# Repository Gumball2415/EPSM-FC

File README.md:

# EPSM-FC

Expansion Port Sound Module for the Famicom

## About

Work in progress!!

This is a version of the EPSM ported for use with the Famicom.

The challenge with the Famicom version is that the device no longer has access
to the extra control signals on the NES expansion port. Most relevant, OUT1,
CPU_A15, and all the EXP pins. This project aims to solve this using extra logic
that can recreate the necessary signals for addressing the EPSM.

## License

This design is licensed under the TAPR Open Hardware License.\
For resale, please contact Pierre Althinsson (Perkka).

Original EPSM is Copyright (C) 2021-2025 Pierre Althinson.\
EPSM-FC is Copyright (C) 2022-2025 Persune.

## Usage

- [NESDev wiki](https://www.nesdev.org/wiki/Expansion_Port_Sound_Module)
- Also see [the original EPSM repo](https://github.com/Perkka2/EPSM/)

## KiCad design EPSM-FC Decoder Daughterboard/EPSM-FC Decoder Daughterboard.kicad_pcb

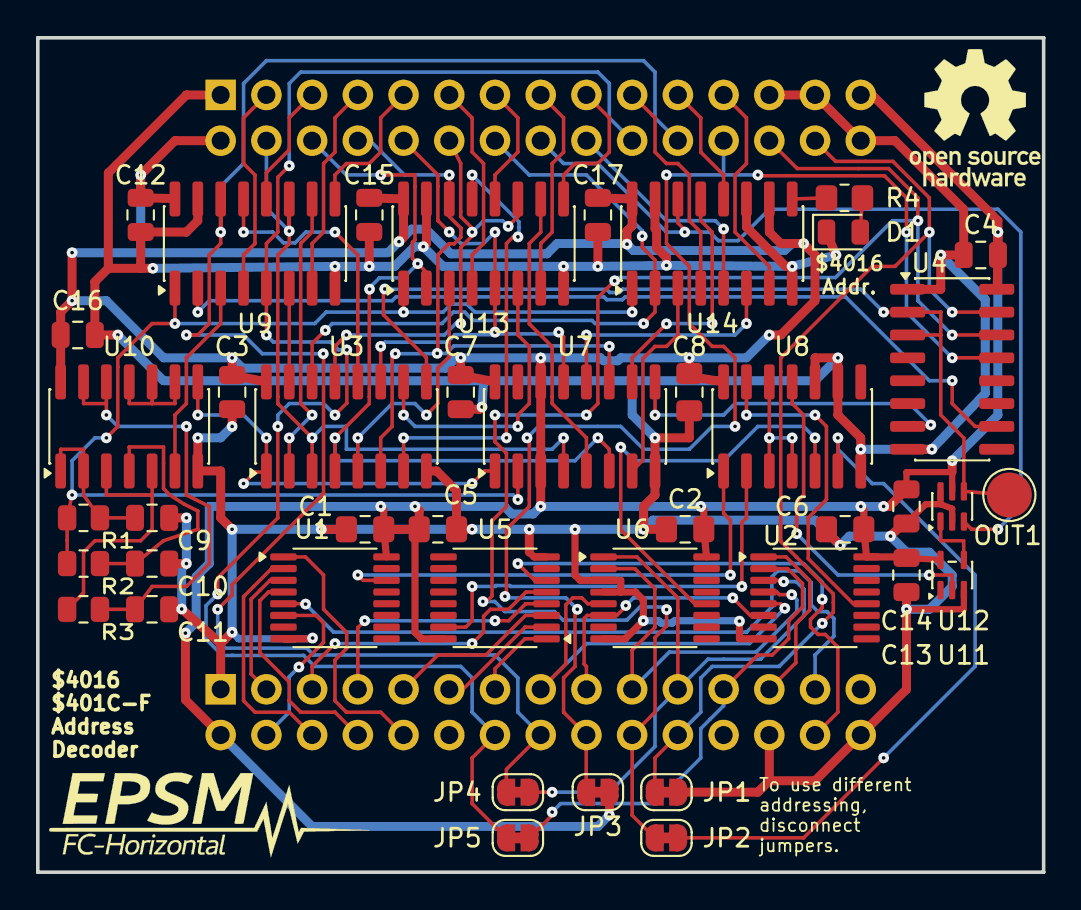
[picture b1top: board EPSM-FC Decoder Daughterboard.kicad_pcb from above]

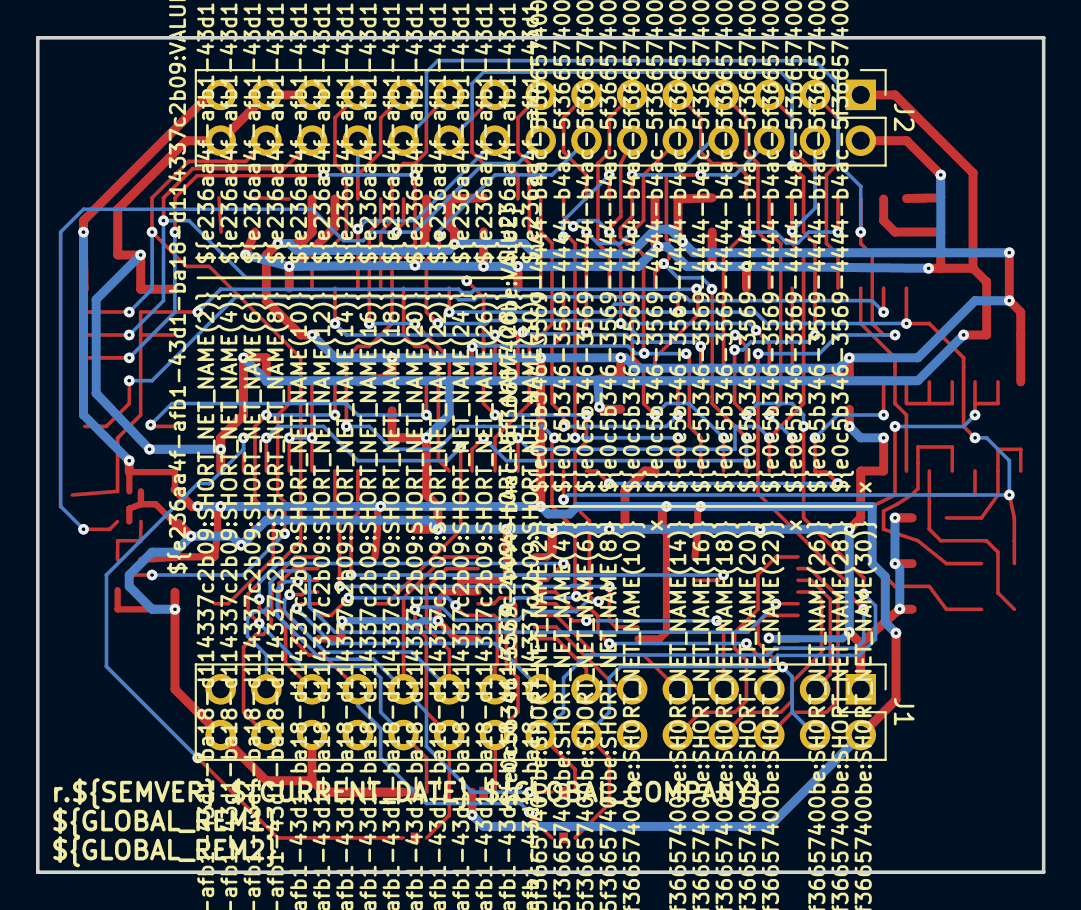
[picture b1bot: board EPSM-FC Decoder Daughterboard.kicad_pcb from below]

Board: 2 copper layers, 55.9 x 46.4 mm, 46 parts (2 on the bottom side), 75 nets.

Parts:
C1, C2, C5, C6, C8: 0.1uF; C_0805_2012Metric_Pad1.18x1.45mm_HandSolder
C3, C4, C7, C12, C13, C14, C15, C16, C17: 0.1u; C_0805_2012Metric
C9, C10, C11: 68p; C_0805_2012Metric
D1: PINK; LED_0805_2012Metric
J1: EPSM_ADDR; PinHeader_2x15_P2.54mm_Vertical
J2: EPSM_DATA; PinHeader_2x15_P2.54mm_Vertical
JP1, JP2, JP3, JP4, JP5: SolderJumper-2_P1.3mm_Bridged_RoundedPad1.0x1.5mm
R1: 3K; R_0805_2012Metric
R2, R3: 1K; R_0805_2012Metric
R4: 330; R_0805_2012Metric_Pad1.20x1.40mm_HandSolder
Ref**: Val**; oshw-logo
Ref**#2: Val**; EPSM_silkscreen
TP1: OUT1; TestPoint_Pad_D2.5mm
U1, U2, U5, U6: 74HC138; TSSOP-16_4.4x5mm_P0.65mm
U3, U7: 74HC174; SOIC-16_3.9x9.9mm_P1.27mm
U4: 74HC139; SOIC-16_3.9x9.9mm_P1.27mm
U8: 74HC32; SOIC-14_3.9x8.7mm_P1.27mm
U9, U13, U14: 74HC157; SOIC-16_3.9x9.9mm_P1.27mm
U10: 74HC132; SOIC-14_3.9x8.7mm_P1.27mm
U11: 74LVC1GU04; SOT-353_SC-70-5
U12: 74LVC1G373; SOT-363_SC-70-6

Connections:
/$40xx_W_~CE: U8.3, U8.4, U8.12
/$40xx_~W_A: U1.14 (~Y1), U8.1
/$40xx_~W_B: U5.15 (~Y0), U8.2
/$401C-F_~CE: U6.12 (~Y3), U8.5
/$401CFW~CE: JP2.1 (A), U8.6
/$4016_P: R1.1, R2.1, U7.2 (Q0), U9.1 (S), U13.1 (S), U14.1 (S)
/$4016_W_CE: U11.4, U12.1 (LE)
/$4016_W_~CE: U8.11, U11.2
/$4016_~CE: U2.12 (~Y3), U8.13
/$4016_~P_DL: R3.1, U10.3, U10.5
/B_CPU_A0: J1.25, U2.1 (A0)
/B_CPU_A1: J1.23, JP5.1 (A), U2.2 (A1)
/B_CPU_A2: J1.21, JP4.1 (A), U2.3 (A2), U6.1 (A0)
/B_CPU_A3: J1.19, U2.4 (~E0), U6.2 (A1)
/B_CPU_A4: J1.17, U2.6 (E2), U6.6 (E2)
/B_CPU_A5: J1.15, U2.5 (~E1), U6.5 (~E1)
/B_CPU_A6: J1.13, U5.1 (A0)
/B_CPU_A7: J1.11, U5.2 (A1)
/B_CPU_A8: J1.9, U5.3 (A2)
/B_CPU_A9: J1.7, U5.4 (~E0)
/B_CPU_A10: J1.5, U5.5 (~E1)
/B_CPU_A11: J1.3, U1.3 (A2)
/B_CPU_A12: J1.6, U1.2 (A1)
/B_CPU_A13: J1.8, U1.4 (~E0)
/B_CPU_A14: J1.10, U1.1 (A0)
/B_CPU_D0: J2.18, U14.5 (I0b)
/B_CPU_D1: J2.16, U12.3 (D), U14.14 (I0d)
/B_CPU_D2: J2.14, U3.14 (D5), U14.2 (I0a)
/B_CPU_D3: J2.12, U3.13 (D4), U13.11 (I0c)
/B_CPU_D4: J2.10, U3.11 (D3), U7.13 (D4), U13.5 (I0b)
/B_CPU_D5: J2.8, U3.6 (D2), U7.11 (D3), U13.14 (I0d)
/B_CPU_D6: J2.6, U3.4 (D1), U7.6 (D2), U13.2 (I0a)
/B_CPU_D7: J2.4, U3.3 (D0), U7.4 (D1), U9.11 (I0c)
/B_CPU_R~W: J1.27, U1.5 (~E1)
/B_M2: J1.4, U1.6 (E2)
/B_~ROMSEL: J1.28, U5.6 (E2)
/EPSM_A0: J1.16, J2.22, JP4.2 (B), U9.14 (I0d)
/EPSM_A1: J1.14, J2.20, JP5.2 (B), U9.5 (I0b)
/EPSM_CE3: J1.18, J2.24, JP3.2 (B), U4.13 (A1)
/EPSM_~CE1: J1.22, J2.28, JP1.2 (B), U4.15 (E)
/EPSM_~CE2: J1.20, J2.26, JP2.2 (B), U4.14 (A0)
/EPSM_~CS: U4.10 (O2), U9.2 (I0a)
/OUT1: TP1.1 (1_1), U3.9 (Cp), U4.2 (A0), U4.3 (A1), U12.4 (Q)
/S_A0: U3.12 (Q4), U9.13 (I1d)
/S_A1: U3.15 (Q5), U9.6 (I1b)
/S_CPU_D0: U7.12 (Q4), U14.6 (I1b)
/S_CPU_D1: U7.10 (Q3), U14.13 (I1d)
/S_CPU_D2: U7.7 (Q2), U14.3 (I1a)
/S_CPU_D3: U7.5 (Q1), U13.10 (I1c)
/S_CPU_D4: U3.10 (Q3), U13.6 (I1b)
/S_CPU_D5: U3.7 (Q2), U13.13 (I1d)
/S_CPU_D6: U3.5 (Q1), U13.3 (I1a)
/S_CPU_D7: U3.2 (Q0), U9.10 (I1c)
/S_~CS: U9.3 (I1a), U10.6
/S_~RST: U3.1 (~Mr), U7.1 (~Mr), U10.8
/YM_A0: J2.5, U9.12 (Zd)
/YM_A1: J2.7, U9.7 (Zb)
/YM_D0: J2.23, U14.7 (Zb)
/YM_D1: J2.21, U14.12 (Zd)
/YM_D2: J2.19, U14.4 (Za)
/YM_D3: J2.17, U13.9 (Zc)
/YM_D4: J2.15, U13.7 (Zb)
/YM_D5: J2.13, U13.12 (Zd)
/YM_D6: J2.11, U13.4 (Za)
/YM_D7: J2.9, U9.9 (Zc)
/YM_~CS: J2.3, U9.4 (Za)
/~OUT1: U4.7 (O3), U7.9 (Cp)
GND: C1.1, C2.1, C3.1, C4.1, C5.1, C6.1, C7.1, C8.1, C9.2, C10.2, C11.2, C12.1, C13.1, C14.1, C15.1, C16.1, C17.1, D1.1 (K), J1.1, J1.26, J1.30, J2.1, J2.25, J2.27, J2.30, JP1.1 (A), U1.8 (GND), U2.8 (GND), U3.8 (GND), U4.1 (E), U4.8 (GND), U5.8 (GND), U6.3 (A2), U6.4 (~E0), U6.8 (GND), U7.8 (GND), U8.7 (GND), U8.9, U8.10, U9.8 (GND), U9.15 (E), U10.7 (GND), U11.3 (GND), U12.2 (GND), U12.6 (~OE), U13.8 (GND), U13.15 (E), U14.8 (GND), U14.11 (I0c), U14.15 (E)
unnamed: C9.1, R1.2, U10.1, U10.2
unnamed: C10.1, R2.2, U10.4
unnamed: C11.1, R3.2, U10.12, U10.13
unnamed: D1.2 (A), R4.2
unnamed: U10.9, U10.10, U10.11
unnamed: R4.1, U14.9 (Zc)
VCC: C1.2, C2.2, C3.2, C4.2, C5.2, C6.2, C7.2, C8.2, C12.2, C13.2, C14.2, C15.2, C16.2, C17.2, J1.2, J2.2, J2.29, JP3.1 (A), U1.16 (VCC), U2.16 (VCC), U3.16 (VCC), U4.16 (VCC), U5.16 (VCC), U6.16 (VCC), U7.3 (D0), U7.14 (D5), U7.16 (VCC), U8.14 (VCC), U9.16 (VCC), U10.14 (VCC), U11.5 (VCC), U12.5 (VCC), U13.16 (VCC), U14.10 (I1c), U14.16 (VCC)

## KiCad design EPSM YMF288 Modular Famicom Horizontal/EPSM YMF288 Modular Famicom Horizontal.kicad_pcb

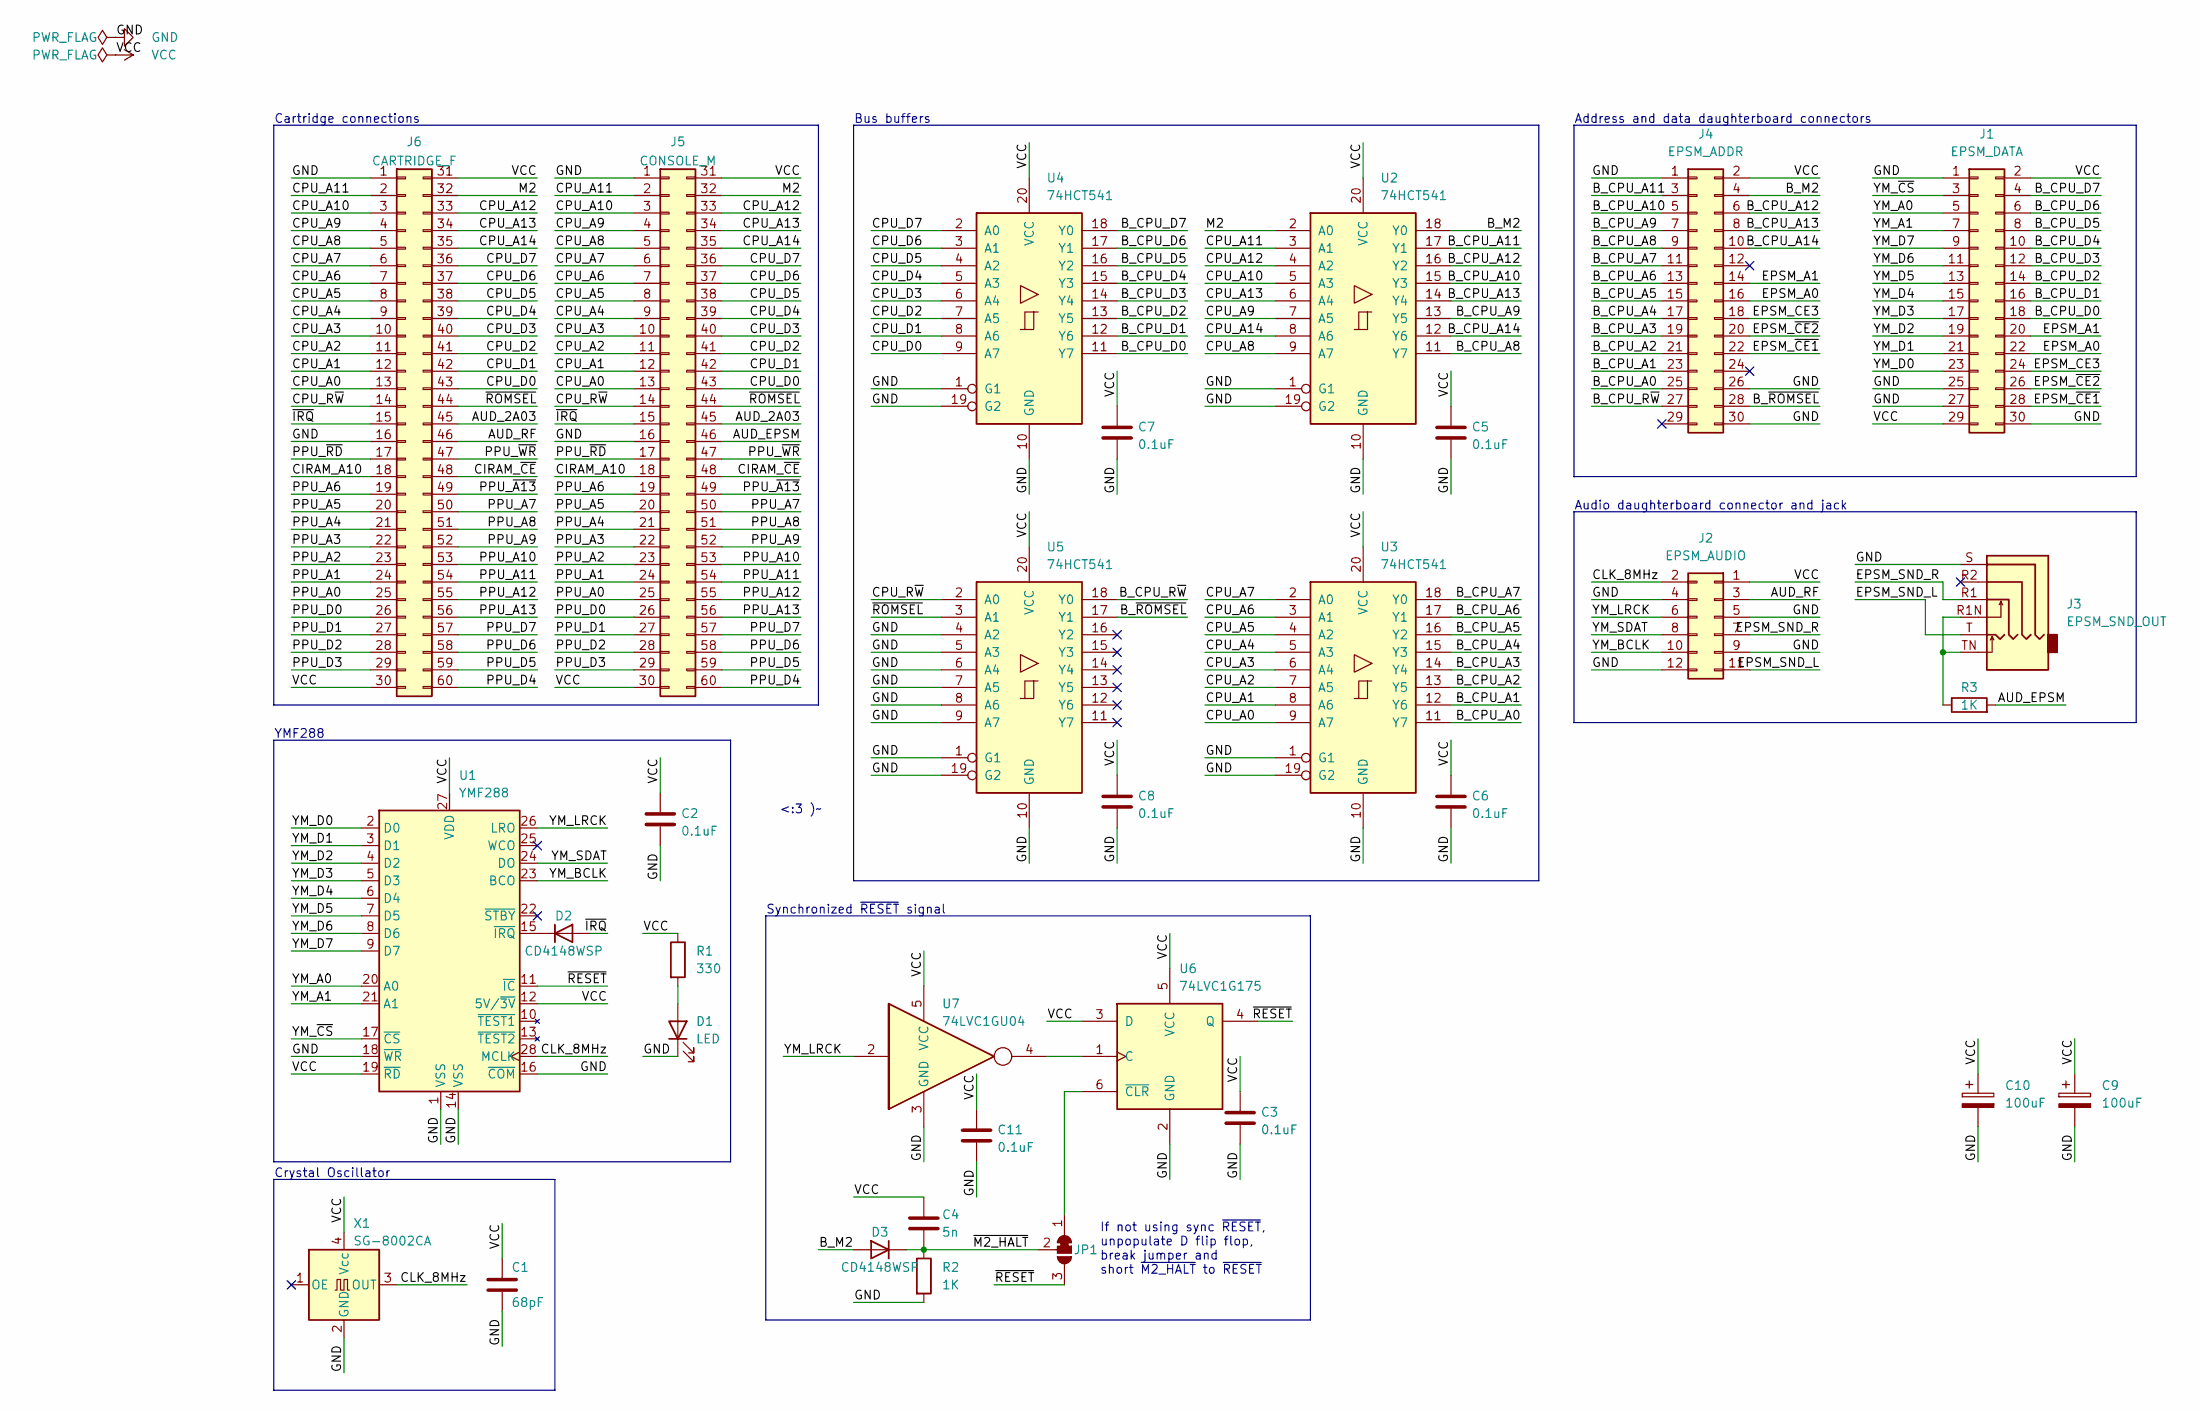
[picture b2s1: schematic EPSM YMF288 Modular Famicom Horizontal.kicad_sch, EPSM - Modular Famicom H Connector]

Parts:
C1: 68pF; C_0805_2012Metric_Pad1.18x1.45mm_HandSolder
C2, C3, C5, C6, C7, C8, C11: 0.1uF; C_0805_2012Metric_Pad1.18x1.45mm_HandSolder
C4: 5n; C_0805_2012Metric_Pad1.18x1.45mm_HandSolder
C9, C10: 100uF; CP_Elec_6.3x5.4
D1: LED; LED_0805_2012Metric
D2, D3: CD4148WSP; D_0805_2012Metric
J1: EPSM_DATA; PinSocket_2x15_P2.54mm_Vertical_SMD
J2: EPSM_AUDIO; PinSocket_2x06_P2.54mm_Vertical_SMD
J3: EPSM_SND_OUT; Jack_3.5mm_PJ311_Horizontal
J4: EPSM_ADDR; PinSocket_2x15_P2.54mm_Vertical_SMD
J5: CONSOLE_M; HVC-ETROM-01
J6: CARTRIDGE_F; FC_CONN_F
JP1: SolderJumper-3_P1.3mm_Bridged12_Pad1.0x1.5mm
R1: 330; R_0805_2012Metric_Pad1.20x1.40mm_HandSolder
R2, R3: 1K; R_0805_2012Metric_Pad1.20x1.40mm_HandSolder
U1: YMF288; SOP-28_8.4x18.1mm_P1.27mm
U2, U3, U4, U5: 74HCT541; TSSOP-20_4.4x6.5mm_P0.65mm
U6: 74LVC1G175; SOT-363_SC-70-6; LCSC C52145624
U7: 74LVC1GU04; SOT-353_SC-70-5; LCSC C53114303
X1: SG-8002CA; Oscillator_SMD_Abracon_ASV-4Pin_7.0x5.1mm

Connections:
/AUD_2A03: J5.45, J6.45
/AUD_EPSM: J5.46, R3.2
/AUD_RF: J2.3, J6.46
/B_CPU_A0: J4.25, U3.11 (Y7)
/B_CPU_A1: J4.23, U3.12 (Y6)
/B_CPU_A2: J4.21, U3.13 (Y5)
/B_CPU_A3: J4.19, U3.14 (Y4)
/B_CPU_A4: J4.17, U3.15 (Y3)
/B_CPU_A5: J4.15, U3.16 (Y2)
/B_CPU_A6: J4.13, U3.17 (Y1)
/B_CPU_A7: J4.11, U3.18 (Y0)
/B_CPU_A8: J4.9, U2.11 (Y7)
/B_CPU_A9: J4.7, U2.13 (Y5)
/B_CPU_A10: J4.5, U2.15 (Y3)
/B_CPU_A11: J4.3, U2.17 (Y1)
/B_CPU_A12: J4.6, U2.16 (Y2)
/B_CPU_A13: J4.8, U2.14 (Y4)
/B_CPU_A14: J4.10, U2.12 (Y6)
/B_CPU_D0: J1.18, U4.11 (Y7)
/B_CPU_D1: J1.16, U4.12 (Y6)
/B_CPU_D2: J1.14, U4.13 (Y5)
/B_CPU_D3: J1.12, U4.14 (Y4)
/B_CPU_D4: J1.10, U4.15 (Y3)
/B_CPU_D5: J1.8, U4.16 (Y2)
/B_CPU_D6: J1.6, U4.17 (Y1)
/B_CPU_D7: J1.4, U4.18 (Y0)
/B_CPU_R~W: J4.27, U5.18 (Y0)
/B_M2: D3.2 (A), J4.4, U2.18 (Y0)
/B_~ROMSEL: J4.28, U5.17 (Y1)
/CIRAM_A10: J5.18, J6.18
/CIRAM_~CE: J5.48, J6.48
/CLK_8MHz: J2.2, U1.28 (MCLK), X1.3 (OUT)
/CPU_A0: J5.13, J6.13, U3.9 (A7)
/CPU_A1: J5.12, J6.12, U3.8 (A6)
/CPU_A2: J5.11, J6.11, U3.7 (A5)
/CPU_A3: J5.10, J6.10, U3.6 (A4)
/CPU_A4: J5.9, J6.9, U3.5 (A3)
/CPU_A5: J5.8, J6.8, U3.4 (A2)
/CPU_A6: J5.7, J6.7, U3.3 (A1)
/CPU_A7: J5.6, J6.6, U3.2 (A0)
/CPU_A8: J5.5, J6.5, U2.9 (A7)
/CPU_A9: J5.4, J6.4, U2.7 (A5)
/CPU_A10: J5.3, J6.3, U2.5 (A3)
/CPU_A11: J5.2, J6.2, U2.3 (A1)
/CPU_A12: J5.33, J6.33, U2.4 (A2)
/CPU_A13: J5.34, J6.34, U2.6 (A4)
/CPU_A14: J5.35, J6.35, U2.8 (A6)
/CPU_D0: J5.43, J6.43, U4.9 (A7)
/CPU_D1: J5.42, J6.42, U4.8 (A6)
/CPU_D2: J5.41, J6.41, U4.7 (A5)
/CPU_D3: J5.40, J6.40, U4.6 (A4)
/CPU_D4: J5.39, J6.39, U4.5 (A3)
/CPU_D5: J5.38, J6.38, U4.4 (A2)
/CPU_D6: J5.37, J6.37, U4.3 (A1)
/CPU_D7: J5.36, J6.36, U4.2 (A0)
/CPU_R~W: J5.14, J6.14, U5.2 (A0)
/EPSM_A0: J1.22, J4.16
/EPSM_A1: J1.20, J4.14
/EPSM_CE3: J1.24, J4.18
/EPSM_SND_L: J2.11, J3.T
/EPSM_SND_R: J2.7, J3.R1
/EPSM_~CE1: J1.28, J4.22
/EPSM_~CE2: J1.26, J4.20
/M2: J5.32, J6.32, U2.2 (A0)
/PPU_A0: J5.25, J6.25
/PPU_A1: J5.24, J6.24
/PPU_A2: J5.23, J6.23
/PPU_A3: J5.22, J6.22
/PPU_A4: J5.21, J6.21
/PPU_A5: J5.20, J6.20
/PPU_A6: J5.19, J6.19
/PPU_A7: J5.50, J6.50
/PPU_A8: J5.51, J6.51
/PPU_A9: J5.52, J6.52
/PPU_A10: J5.53, J6.53
/PPU_A11: J5.54, J6.54
/PPU_A12: J5.55, J6.55
/PPU_A13: J5.56, J6.56
/PPU_D0: J5.26, J6.26
/PPU_D1: J5.27, J6.27
/PPU_D2: J5.28, J6.28
/PPU_D3: J5.29, J6.29
/PPU_D4: J5.60, J6.60
/PPU_D5: J5.59, J6.59
/PPU_D6: J5.58, J6.58
/PPU_D7: J5.57, J6.57
/PPU_~A13: J5.49, J6.49
/PPU_~RD: J5.17, J6.17
/PPU_~WR: J5.47, J6.47
/YM_A0: J1.5, U1.20 (A0)
/YM_A1: J1.7, U1.21 (A1)
/YM_BCLK: J2.10, U1.23 (BCO)
/YM_D0: J1.23, U1.2 (D0)
/YM_D1: J1.21, U1.3 (D1)
/YM_D2: J1.19, U1.4 (D2)
/YM_D3: J1.17, U1.5 (D3)
/YM_D4: J1.15, U1.6 (D4)
/YM_D5: J1.13, U1.7 (D5)
/YM_D6: J1.11, U1.8 (D6)
/YM_D7: J1.9, U1.9 (D7)
/YM_LRCK: J2.6, U1.26 (LRO), U7.2
/YM_SDAT: J2.8, U1.24 (DO)
/YM_~CS: J1.3, U1.17 (~CS)
/~IRQ: D2.2 (A), J5.15, J6.15
/~M2_HALT: C4.1, D3.1 (K), JP1.2 (C), R2.1
/~RESET: JP1.3 (B), U1.11 (~IC), U6.4 (Q)
/~ROMSEL: J5.44, J6.44, U5.3 (A1)
GND: C1.2, C2.1, C3.1, C5.1, C6.1, C7.1, C8.1, C9.2, C10.2, C11.1, D1.1 (K), J1.1, J1.25, J1.27, J1.30, J2.4, J2.5, J2.9, J2.12, J3.S, J4.1, J4.26, J4.30, J5.1, J5.16, J6.1, J6.16, R2.2, U1.1 (VSS), U1.14 (VSS), U1.16 (~COM), U1.18 (~WR), U2.1 (G1), U2.10 (GND), U2.19 (G2), U3.1 (G1), U3.10 (GND), U3.19 (G2), U4.1 (G1), U4.10 (GND), U4.19 (G2), U5.1 (G1), U5.4 (A2), U5.5 (A3), U5.6 (A4), U5.7 (A5), U5.8 (A6), U5.9 (A7), U5.10 (GND), U5.19 (G2), U6.2 (GND), U7.3 (GND), X1.2 (GND)
unnamed: D1.2 (A), R1.2
unnamed: D2.1 (K), U1.15 (~IRQ)
unnamed: J3.R1N, J3.TN, R3.1
unnamed: JP1.1 (A), U6.6 (~CLR)
unnamed: U6.1 (C), U7.4
VCC: C1.1, C2.2, C3.2, C4.2, C5.2, C6.2, C7.2, C8.2, C9.1, C10.1, C11.2, J1.2, J1.29, J2.1, J4.2, J5.30, J5.31, J6.30, J6.31, R1.1, U1.12 (5V/~3V), U1.19 (~RD), U1.27 (VDD), U2.20 (VCC), U3.20 (VCC), U4.20 (VCC), U5.20 (VCC), U6.3 (D), U6.5 (VCC), U7.5 (VCC), X1.4 (Vcc)

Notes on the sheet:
Bus buffers
Synchronized ~{RESET} signal
If not using sync ~{RESET}, unpopulate D flip flop, break jumper and short ~{M2_HALT} to ~{RESET}
Address and data daughterboard connectors
<:3 )~
YMF288
Crystal Oscillator
Audio daughterboard connector and jack
Cartridge connections

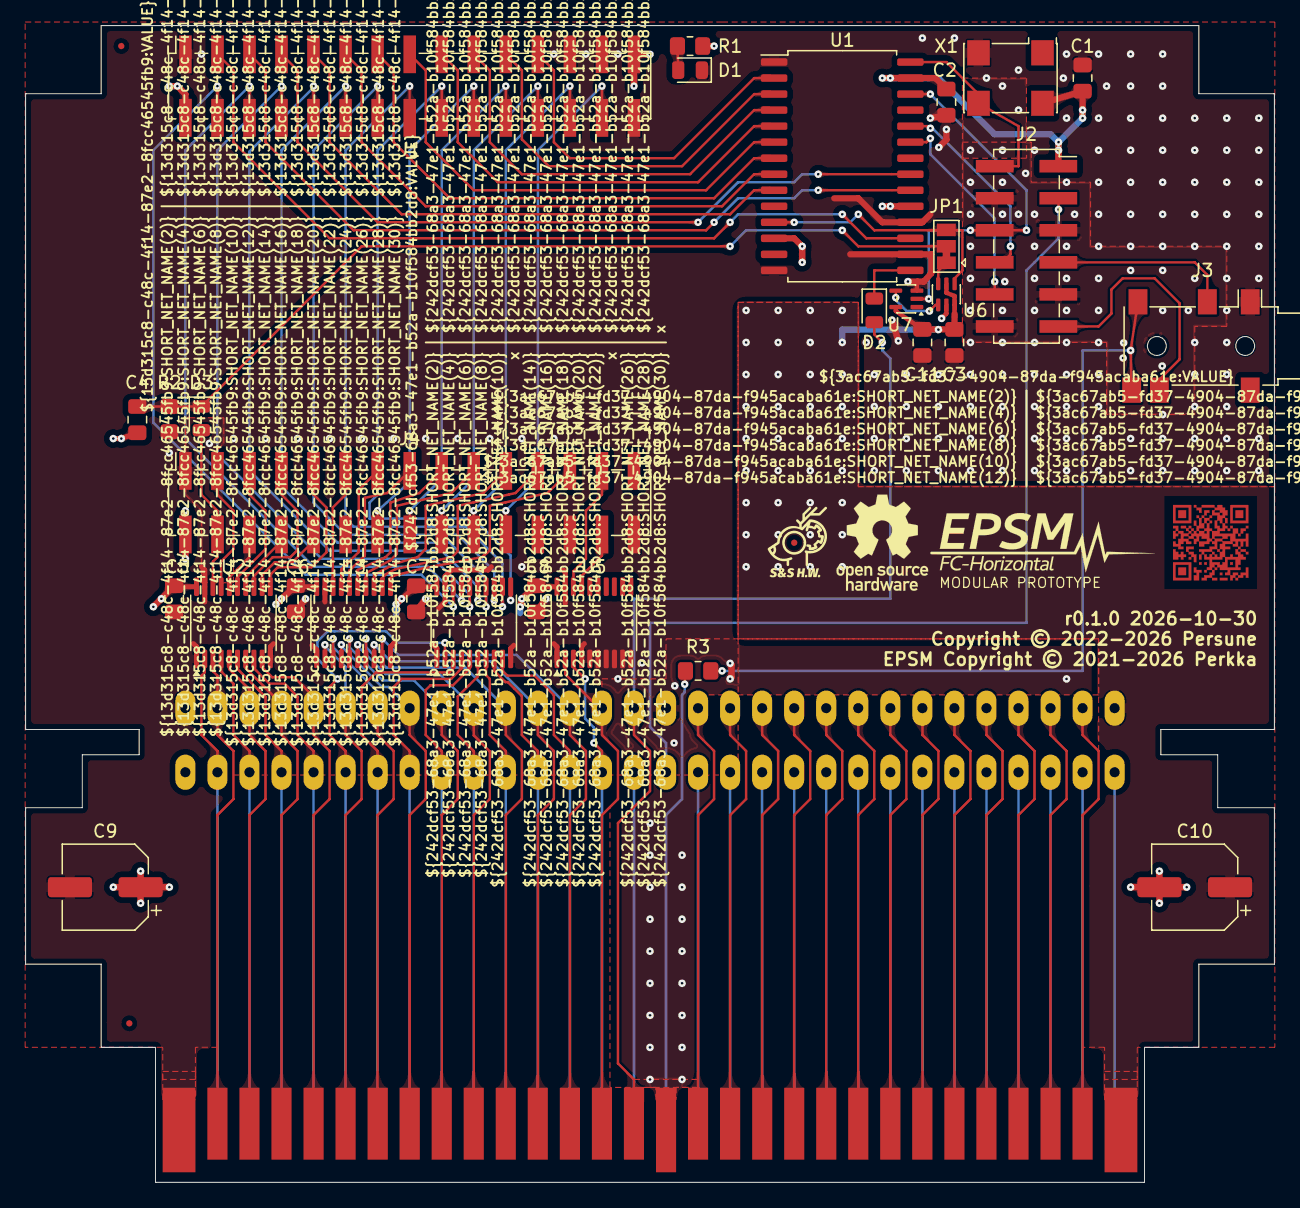
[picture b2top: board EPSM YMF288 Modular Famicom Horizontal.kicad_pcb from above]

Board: 2 copper layers, 99.0 x 91.7 mm, 36 parts (1 on the bottom side), 114 nets.

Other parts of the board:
Ref**: Val**; EPSM_silkscreen
Ref**#2: Val**; oshw-logo
Ref**#3: Val**; qr
svg2mod: G***; maustech icon fiducial 0-50mm 1-50mm

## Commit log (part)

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2025-04-16 Rename license file
2025-04-18 Adjust routing

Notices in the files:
EPSM YMF288 Modular Famicom Horizontal/EPSM YMF288 Modular Famicom Horizontal.kicad_pcb:
Copyright © 2022-2026 Persune
EPSM Copyright © 2021-2026 Perkka
EPSM YMF288 Modular Famicom Horizontal/EPSM YMF288 Modular Famicom Horizontal.kicad_sch:
EPSM Copyright 2021-2026 Perkka
